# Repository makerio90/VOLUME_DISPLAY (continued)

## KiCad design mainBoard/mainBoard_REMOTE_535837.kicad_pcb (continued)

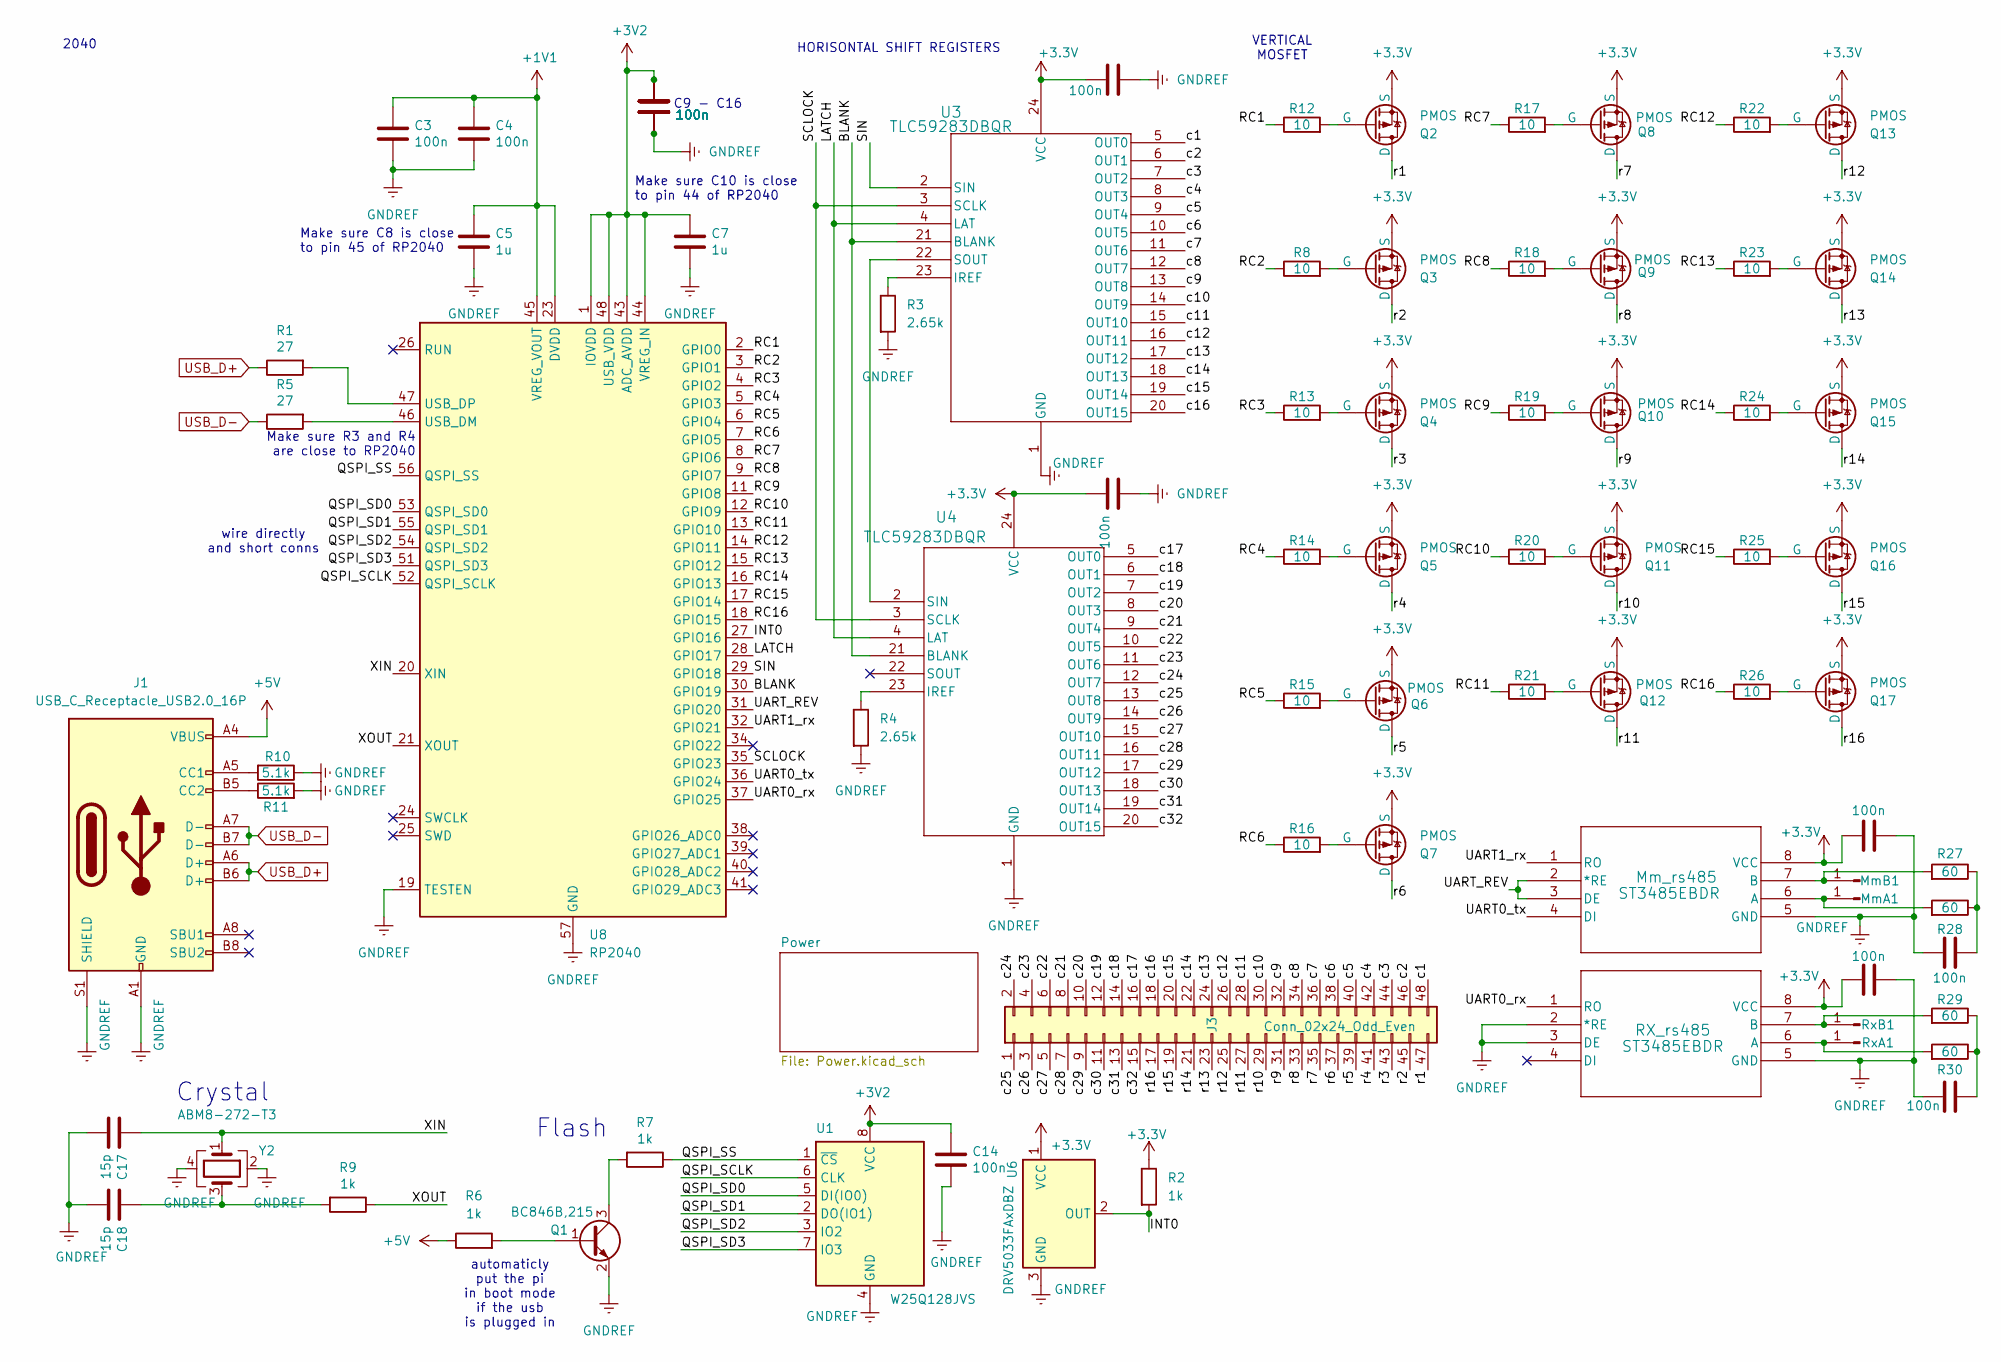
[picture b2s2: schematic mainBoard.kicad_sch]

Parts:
C3, C4, C6, C8, C9, C10, C11, C12, C13, C14, C15, C20, C21, C22, C23, C24: 100n; C_0402_1005Metric; MPN CL05B104KO5NNNC; LCSC PN C1525
C5, C7: 1u; C_0402_1005Metric; MPN CL05A105KP5NNNC; LCSC PN C14445
C17, C18: 15p; C_0402_1005Metric; MPN CL05C150JB51PNC; LCSC PN C307341
J1: USB_C_Receptacle_USB2.0_16P; USB_C_Receptacle_G-Switch_GT-USB-7010ASV; MPN GT-USB-7010ASV; LCSC PN C2988369
J3: Conn_02x24_Odd_Even; PinHeader_2x24_P2.54mm_Vertical
MmA1: Conn_01x01_Pin; PinHeader_1x01_P2.54mm_Vertical
MmB1: Conn_01x01_Pin; PinHeader_1x01_P2.54mm_Vertical
Mm_rs485: ST3485EBDR; SO-8_STM; MPN ST3485EBDR; LCSC PN C75809
Q1: BC846B,215; SOT-323_SC-70; MPN BC846B,215; LCSC PN C87062
Q2, Q3, Q4, Q5, Q6, Q7, Q8, Q9, Q10, Q11, Q12, Q13, Q14, Q15, Q16, Q17: PMOS; SOT-416; MPN NTA4151PT1G; LCSC PN C54876
R1, R5: 27; R_0402_1005Metric; MPN WR04X270JTL; LCSC PN C384351
R2, R6, R7, R9: 1k; R_0402_1005Metric; MPN RTT02102JTH; LCSC PN C102758
R3, R4: 2.65k; R_0402_1005Metric; MPN RC-02U2R61FT; LCSC PN C321166
R8, R12, R13, R14, R15, R16, R17, R18, R19, R20, R21, R22, R23, R24, R25, R26: 10; R_0402_1005Metric; MPN CR0402FF10R0G; LCSC PN C100206
R10, R11: 5.1k; R_0402_1005Metric; MPN FCR0402F5K1; LCSC PN C5913162
R27, R28, R29, R30: 60; R_0402_1005Metric; MPN CC0402KRX7R7BB104; LCSC PN C60474
RX_rs485: ST3485EBDR; SO-8_STM; MPN ST3485EBDR; LCSC PN C75809
RxA1: Conn_01x01_Pin; PinHeader_1x01_P2.54mm_Vertical
RxB1: Conn_01x01_Pin; PinHeader_1x01_P2.54mm_Vertical
U1: W25Q128JVS; WFDFPN-8-1EP_3x2mm_P0.5mm_EP1.25x1.35mm; MPN W25Q128JVPIQ; LCSC PN C190862
U3, U4: TLC59283DBQR; DBQ24_TEX; MPN TLC59283DBQR; LCSC PN C702075
U6: DRV5033FAxDBZ; SOT-23; MPN DRV5033FAQDBZR; LCSC PN C2869057
U8: RP2040; QFN-56-1EP_7x7mm_P0.4mm_EP3.2x3.2mm; MPN RP2040; LCSC PN C2040
Y2: ABM8-272-T3; Crystal_SMD_3225-4Pin_3.2x2.5mm; MPN ABM8-272-T3; LCSC PN C20625731

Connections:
+1V1: C3.1, C4.1, C5.1, U8.23 (DVDD), U8.45 (VREG_VOUT), U8.50 (DVDD)
+3.3V: C15.2, C20.2, C21.2, C22.2, Mm_rs485.8 (VCC), Q2.3 (S), Q3.3 (S), Q4.3 (S), Q5.3 (S), Q6.3 (S), Q7.3 (S), Q8.3 (S), Q9.3 (S), Q10.3 (S), Q11.3 (S), Q12.3 (S), Q13.3 (S), Q14.3 (S), Q15.3 (S), Q16.3 (S), Q17.3 (S), R2.1, RX_rs485.8 (VCC), U3.24 (VCC), U4.24 (VCC), U6.1 (VCC); also elsewhere on the board
+3V2: C6.1, C7.1, C8.1, C9.1, C10.1, C11.1, C12.1, C13.1, C14.1, U1.8 (VCC), U8.1 (IOVDD), U8.10 (IOVDD), U8.22 (IOVDD), U8.33 (IOVDD), U8.42 (IOVDD), U8.43 (ADC_AVDD), U8.44 (VREG_IN), U8.48 (USB_VDD), U8.49 (IOVDD); also elsewhere on the board
+5V: J1.A4 (VBUS), J1.A9 (VBUS), J1.B4 (VBUS), J1.B9 (VBUS), R6.1; also elsewhere on the board
/BLANK: U3.21 (BLANK), U4.21 (BLANK), U8.30 (GPIO19)
/INT0: R2.2, U6.2 (OUT), U8.27 (GPIO16)
/LATCH: U3.4 (LAT), U4.4 (LAT), U8.28 (GPIO17)
/QSPI_SCLK: U1.6 (CLK), U8.52 (QSPI_SCLK)
/QSPI_SD0: U1.5 (DI(IO0)), U8.53 (QSPI_SD0)
/QSPI_SD1: U1.2 (DO(IO1)), U8.55 (QSPI_SD1)
/QSPI_SD2: U1.3 (IO2), U8.54 (QSPI_SD2)
/QSPI_SD3: U1.7 (IO3), U8.51 (QSPI_SD3)
/QSPI_SS: R7.1, U1.1 (~CS), U8.56 (QSPI_SS)
/RC1: R12.1, U8.2 (GPIO0)
/RC2: R8.1, U8.3 (GPIO1)
/RC3: R13.1, U8.4 (GPIO2)
/RC4: R14.1, U8.5 (GPIO3)
/RC5: R15.1, U8.6 (GPIO4)
/RC6: R16.1, U8.7 (GPIO5)
/RC7: R17.1, U8.8 (GPIO6)
/RC8: R18.1, U8.9 (GPIO7)
/RC9: R19.1, U8.11 (GPIO8)
/RC10: R20.1, U8.12 (GPIO9)
/RC11: R21.1, U8.13 (GPIO10)
/RC12: R22.1, U8.14 (GPIO11)
/RC13: R23.1, U8.15 (GPIO12)
/RC14: R24.1, U8.16 (GPIO13)
/RC15: R25.1, U8.17 (GPIO14)
/RC16: R26.1, U8.18 (GPIO15)
/SCLOCK: U3.3 (SCLK), U4.3 (SCLK), U8.35 (GPIO23)
/SIN: U3.2 (SIN), U8.29 (GPIO18)
/UART0_rx: RX_rs485.1 (RO), U8.37 (GPIO25)
/UART0_tx: Mm_rs485.4 (DI), U8.36 (GPIO24)
/UART1_rx: Mm_rs485.1 (RO), U8.32 (GPIO21)
/UART_REV: Mm_rs485.2 (*RE), Mm_rs485.3 (DE), U8.31 (GPIO20)
/XIN: C17.1, U8.20 (XIN), Y2.1
/XOUT: R9.1, U8.21 (XOUT)
/c1: J3.48, U3.5 (OUT0)
/c2: J3.46, U3.6 (OUT1)
/c3: J3.44, U3.7 (OUT2)
/c4: J3.42, U3.8 (OUT3)
/c5: J3.40, U3.9 (OUT4)
/c6: J3.38, U3.10 (OUT5)
/c7: J3.36, U3.11 (OUT6)
/c8: J3.34, U3.12 (OUT7)
/c9: J3.32, U3.13 (OUT8)
/c10: J3.30, U3.14 (OUT9)
/c11: J3.28, U3.15 (OUT10)
/c12: J3.26, U3.16 (OUT11)
/c13: J3.24, U3.17 (OUT12)
/c14: J3.22, U3.18 (OUT13)
/c15: J3.20, U3.19 (OUT14)
/c16: J3.18, U3.20 (OUT15)
/c17: J3.16, U4.5 (OUT0)
/c18: J3.14, U4.6 (OUT1)
/c19: J3.12, U4.7 (OUT2)
/c20: J3.10, U4.8 (OUT3)
/c21: J3.8, U4.9 (OUT4)
/c22: J3.6, U4.10 (OUT5)
/c23: J3.4, U4.11 (OUT6)
/c24: J3.2, U4.12 (OUT7)
/c25: J3.1, U4.13 (OUT8)
/c26: J3.3, U4.14 (OUT9)
/c27: J3.5, U4.15 (OUT10)
/c28: J3.7, U4.16 (OUT11)
/c29: J3.9, U4.17 (OUT12)
/c30: J3.11, U4.18 (OUT13)
/c31: J3.13, U4.19 (OUT14)
/c32: J3.15, U4.20 (OUT15)
/r1: J3.47, Q2.1 (D)
/r2: J3.45, Q3.1 (D)
/r3: J3.43, Q4.1 (D)
/r4: J3.41, Q5.1 (D)
/r5: J3.39, Q6.1 (D)
/r6: J3.37, Q7.1 (D)
/r7: J3.35, Q8.1 (D)
/r8: J3.33, Q9.1 (D)
/r9: J3.31, Q10.1 (D)
/r10: J3.29, Q11.1 (D)
/r11: J3.27, Q12.1 (D)
/r12: J3.25, Q13.1 (D)
/r13: J3.23, Q14.1 (D)
/r14: J3.21, Q15.1 (D)
/r15: J3.19, Q16.1 (D)
/r16: J3.17, Q17.1 (D)
GNDREF: C3.2, C4.2, C5.2, C6.2, C7.2, C8.2, C9.2, C10.2, C11.2, C12.2, C13.2, C14.2, C15.1, C17.2, C18.2, C20.1, C21.1, C22.1, C23.2, C24.1, J1.A1 (GND), J1.A12 (GND), J1.B1 (GND), J1.B12 (GND), J1.S1 (SHIELD), Mm_rs485.5 (GND), Q1.2 (E), R3.2, R4.2, R10.1, R11.2, RX_rs485.2 (*RE), RX_rs485.3 (DE), RX_rs485.5 (GND), U1.4 (GND), U3.1 (GND), U4.1 (GND), U6.3 (GND), U8.19 (TESTEN), U8.57 (GND), Y2.2, Y2.4; also elsewhere on the board
unnamed: C18.1, R9.2, Y2.3
unnamed: C23.1, R27.1, R28.1
unnamed: C24.2, R29.1, R30.1
unnamed: J1.A5 (CC1), R10.2
unnamed: J1.B5 (CC2), R11.1
unnamed: MmA1.1, Mm_rs485.6 (A), R28.2
unnamed: MmB1.1, Mm_rs485.7 (B), R27.2
unnamed: Q1.1 (B), R6.2
unnamed: Q1.3 (C), R7.2
unnamed: Q2.2 (G), R12.2
unnamed: Q3.2 (G), R8.2
unnamed: Q4.2 (G), R13.2
unnamed: Q5.2 (G), R14.2
unnamed: Q6.2 (G), R15.2
unnamed: Q7.2 (G), R16.2
unnamed: Q8.2 (G), R17.2
unnamed: Q9.2 (G), R18.2
unnamed: Q10.2 (G), R19.2
unnamed: Q11.2 (G), R20.2
unnamed: Q12.2 (G), R21.2
unnamed: Q13.2 (G), R22.2
unnamed: Q14.2 (G), R23.2
unnamed: Q15.2 (G), R24.2
unnamed: Q16.2 (G), R25.2
unnamed: Q17.2 (G), R26.2
unnamed: R30.2, RX_rs485.6 (A), RxA1.1
unnamed: R29.2, RX_rs485.7 (B), RxB1.1
unnamed: R3.1, U3.23 (IREF)
unnamed: U3.22 (SOUT), U4.2 (SIN)
unnamed: R4.1, U4.23 (IREF)
unnamed: R5.2, U8.46 (USB_DM)
unnamed: R1.2, U8.47 (USB_DP)
USB_D+: J1.A6 (D+), J1.B6 (D+), R1.1
USB_D-: J1.A7 (D-), J1.B7 (D-), R5.1

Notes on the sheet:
HORISONTAL SHIFT REGISTERS
Flash
Crystal
2040
VERTICAL MOSFET
automaticly put the pi in boot mode if the usb is plugged in
Make sure C10 is close to pin 44 of RP2040
wire directly and short conns
C9 - C16
Make sure C8 is close to pin 45 of RP2040
Make sure R3 and R4 are close to RP2040

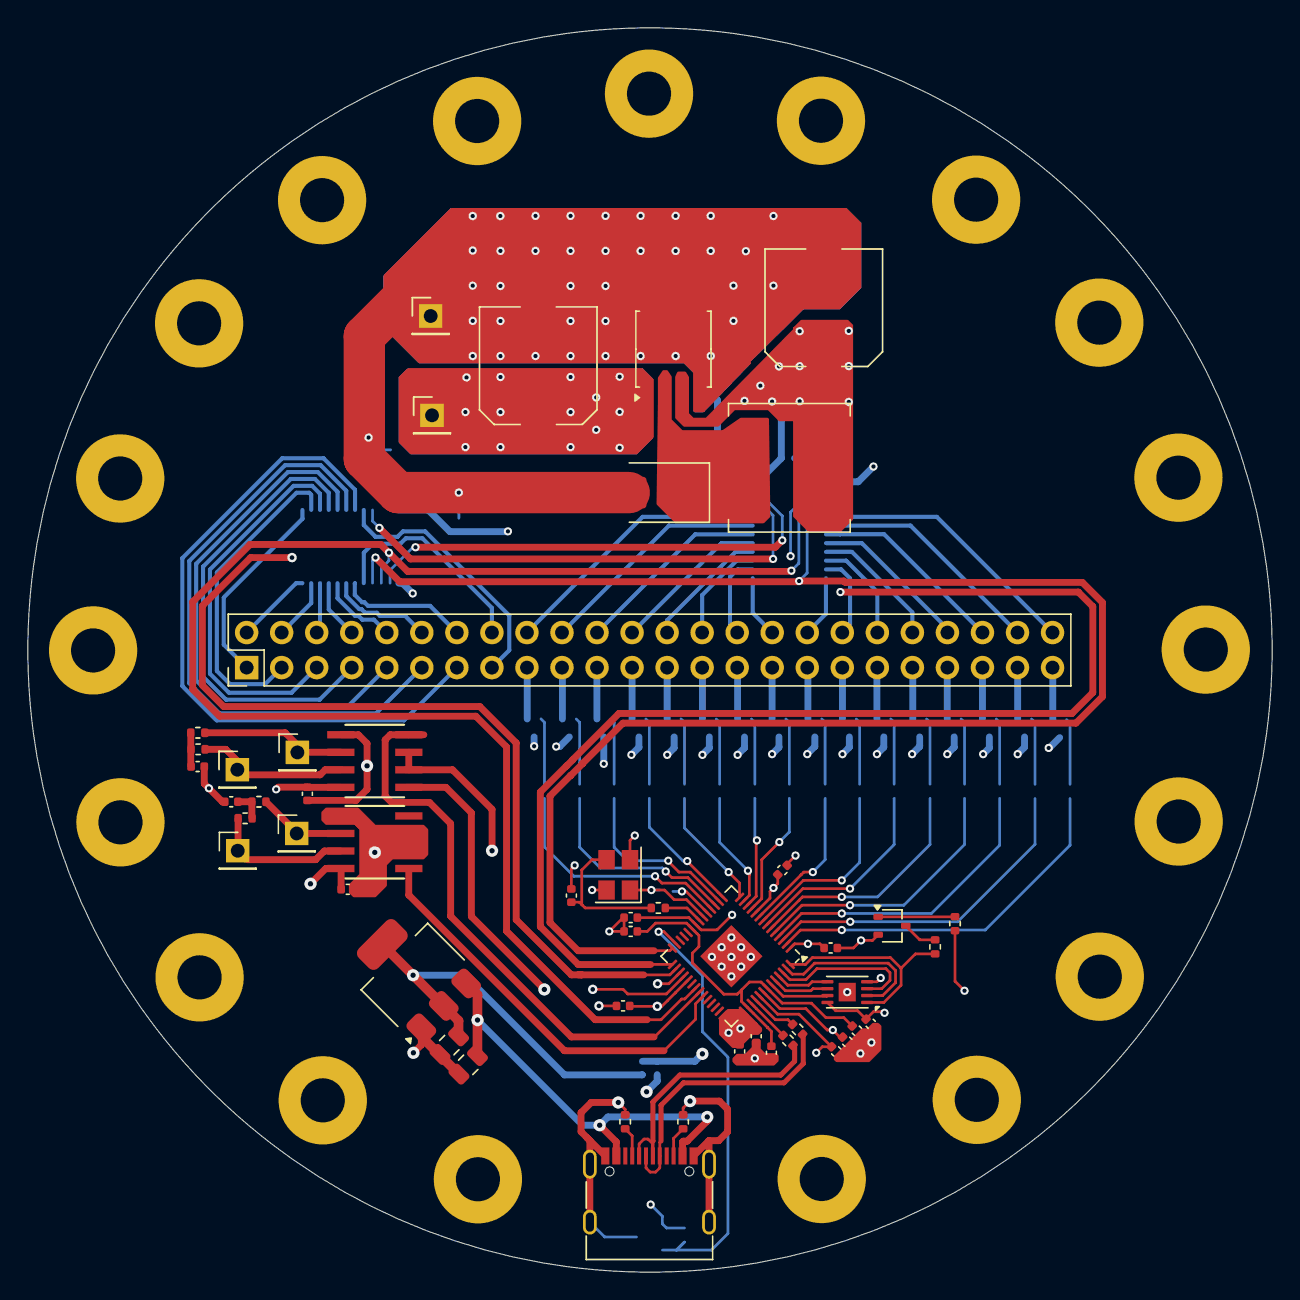
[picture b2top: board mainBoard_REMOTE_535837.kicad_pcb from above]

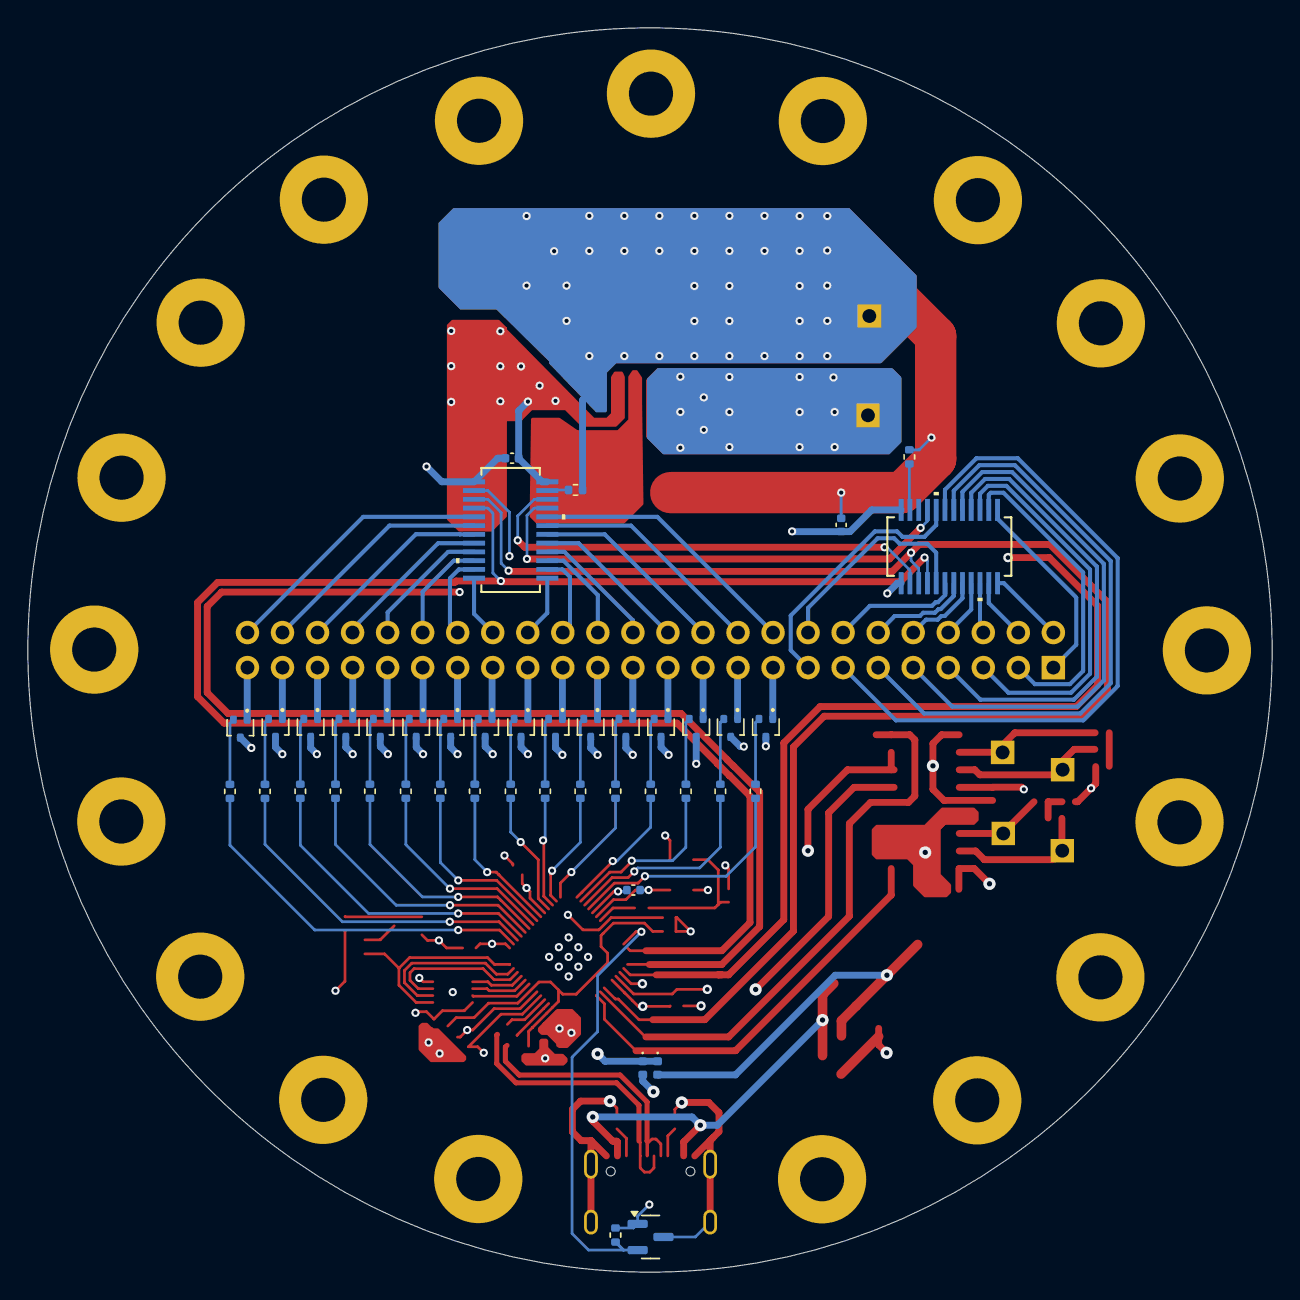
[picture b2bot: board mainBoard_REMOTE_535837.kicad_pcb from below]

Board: 4 copper layers, 90.2 x 90.2 mm, 93 parts (43 on the bottom side), 123 nets.

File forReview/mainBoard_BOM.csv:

"Quantity","Comment","Designator","Footprint","LCSC PN","MPN","Manufacturer"
"2","10u","C1,C2","Capacitor_SMD:C_0805_2012Metric","C15850","CL21A106KAYNNNE"," Samsung Electro-Mechanics "
"2","470uF","C16,C19","Capacitor_SMD:C_Elec_8x10.2","C343909","EEEFP1C471AP"," PANASONIC"
"2","15p","C17,C18","Capacitor_SMD:C_0402_1005Metric","C307341","CL05C150JB51PNC","Samsung Electro-Mechanics"
"14","100n","C3,C4,C6,C8,C9,C10,C11,C12,C13,C14,C15,C20,C21,C22","Capacitor_SMD:C_0402_1005Metric","C1525","CL05B104KO5NNNC"," Samsung Electro-Mechanics "
"2","1u","C5,C7","Capacitor_SMD:C_0402_1005Metric","C14445","CL05A105KP5NNNC","Samsung Electro-Mechanics "
"1","D_Schottky","D2","Diode_SMD:D_SMB","C28642302","TPNSR05F40NXT5G"," TECH PUBLIC"
"2","D","D1,D3","Diode_SMD:D_0402_1005Metric","C703125","LQW15AN12NH00D"," Murata Electronics"
"1","USB_C_Receptacle_USB2.0_16P","J1","Connector_USB:USB_C_Receptacle_G-Switch_GT-USB-7010ASV","C2988369","GT-USB-7010ASV","G-Switch"
"1","SDCHA1V8040-470-R","L1","Inductor_SMD:L_Coilcraft_XAL8080-XXX","C17221881","SDCHA1V8040-470-R","  EATON "
"2","ST3485EBDR","Mm_rs485,RX_rs485","footprints:SO-8_STM","C75809","ST3485EBDR"," STMicroelectronics"
"1","BC846B,215","Q1","Package_TO_SOT_SMD:SOT-323_SC-70","C87062","BC846B,215","Nexperia "
"16","PMOS","Q2,Q3,Q4,Q5,Q6,Q7,Q8,Q9,Q10,Q11,Q12,Q13,Q14,Q15,Q16,Q17","Package_TO_SOT_SMD:SOT-416","C54876","NTA4151PT1G ","onsemi"
"2","27","R1,R5","Resistor_SMD:R_0402_1005Metric","C384351","WR04X270JTL"," Walsin Tech Corp"
"2","5.1k","R10,R11","Resistor_SMD:R_0402_1005Metric","C5913162","FCR0402F5K1","VO"
"4","1k","R2,R6,R7,R9","Resistor_SMD:R_0402_1005Metric","C102758","RTT02102JTH"," RALEC"
"2","2.65k","R3,R4","Resistor_SMD:R_0402_1005Metric","C321166","RC-02U2R61FT","RC-02U2R61FT"
"16","10","R8,R12,R13,R14,R15,R16,R17,R18,R19,R20,R21,R22,R23,R24,R25,R26","Resistor_SMD:R_0402_1005Metric","C100206","CR0402FF10R0G"," LIZ Elec"
"1","W25Q128JVS","U1","Package_DFN_QFN:WFDFPN-8-1EP_3x2mm_P0.5mm_EP1.25x1.35mm","C190862","W25Q128JVPIQ","Winbond Electronics"
"1","NCP1117-3.3_SOT223","U5","Package_TO_SOT_SMD:SOT-223-3_TabPin2","C98965","NCP1117ST12T3G"," onsemi"
"1","DRV5033FAxDBZ","U6","Package_TO_SOT_SMD:SOT-23","C2869057","DRV5033FAQDBZR"," Texas Instruments "
"1","AP1509","U7","Package_SO:SOP-8_5.28x5.23mm_P1.27mm","C151822","AP1509-SG-13"," Diodes Incorporated "
"1","RP2040","U8","Package_DFN_QFN:QFN-56-1EP_7x7mm_P0.4mm_EP3.2x3.2mm","C2040","RP2040"," Raspberry Pi "
"2","TLC59283DBQR","U3,U4","DBQ24_TEX:DBQ24_TEX","C702075","TLC59283DBQR","Texas Instruments"
"1","ABM8-272-T3","Y2","Crystal:Crystal_SMD_3225-4Pin_3.2x2.5mm","C20625731","ABM8-272-T3","  Abracon LLC "

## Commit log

2024-11-02 all existing work
2024-11-02 add files for rieview
2024-11-10 getting ready for another review
2025-01-31 changes made on laptop
2025-01-31 changes made on desktop
2025-01-31 some more files
2025-01-31 fuck conflicts, just go back to what was on my pc
